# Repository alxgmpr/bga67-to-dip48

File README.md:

# bga67-to-dip48

Reusable bridge between the Google Home Mini's VFBGA67 NAND lands and a commercial XGecu
BGA-to-DIP48 socket adapter.

The architecture is intentionally asymmetric:

```text
PROGRAM                          BOOT / TEST

XGecu programmer                Google Home motherboard
       ^                                  ^
       | DIP48                            | solder balls
[ XGecu adapter ]                 [ chipless carrier A ]
[ actual NAND   ]                         |
       |                                 | DF40 service joint
       +------------------------> [ socket base B ]
                                  [ DIP48 receptacle ]
```

The actual NAND remains clamped in the XGecu adapter. That adapter/NAND assembly moves
between the programmer and board B. Board A is a permanent, chipless interposer soldered to
the Google motherboard; it has no NAND package and no sacrificial memory.

| Board | Contents | Nominal size |
|---|---|---:|
| `carrier/` | mirrored VFBGA67 motherboard lands + DF40 plug | 8.41 × 7.60 mm |
| `base/` | DIP48 socket for XGecu adapter + DF40 receptacle + passives | 27.78 × 61.38 mm |
| `chip/` | real VFBGA67 lands + DF40 receptacle, NAND soldered here | 8.41 × 7.60 mm |
| `prog/` | DF40 plug + DIP48 male pins for the XGecu T76 ZIF | 27.78 × 61.38 mm |

## Compact routed carrier

Board A follows the useful parts of Courk's original NandBug routing topology:

- the current compact 8.41 × 7.60 mm outline;
- top-side DF40 within 0.20 mm of the bottom-side mirrored VFBGA67 field centre;
- the completed carrier routing preserved as the canonical DF40 electrical order;
- one short diagonal dogbone from each used VFBGA67 land;
- ordinary 0.45 mm vias with 0.20 mm finished drills;
- no blind/buried vias, microvias, via-in-pad, fill/cap, or HDI process.

That last point holds for boards A, B and D. **Board C is the deliberate exception** — see
"Via-in-pad on board C" below.

The manufacturing target is a standard JLCPCB four-layer stackup, 1.6 mm, ENIG.

The 47 unused motherboard lands remain floating. `U1` is only a logical pin map and mirrored
land interface; it is excluded from BOM/position output and has no NAND model or package
graphics.

The carrier and the base are both routed. Base DRC reports zero unconnected items and zero
schematic parity issues; its remaining 20 warnings are all `text thickness out of range` on
silkscreen and are cosmetic.

## Via-in-pad on board C

Board C is the only board that puts vias inside BGA lands. The NAND is reflowed onto those
lands, which forces the choice:

- a soldermask-plugged via is not flat enough to print a stencil against when reballing;
- an untented via wicks solder out of the ball joint.

So board C's in-pad vias use JLCPCB's **Epoxy Filled & Capped** process: resin filled, baked,
levelled, then copper plated over to a flat surface. Via diameters must be 0.15–0.55 mm and
the vias must carry no soldermask opening on either face.

> **Pre-order gate.** JLCPCB document Epoxy Filled & Capped as the default at **6 layers and
> above** and do not list it as a standard 4-layer option. Board C is 4-layer. Confirm with
> JLCPCB that the process is available on a 4-layer order, and at what price, **before
> fabricating board C**. If it is not, the options are moving board C to 6 layers or routing
> the in-pad vias back out to dogbones.

Boards A, B and D remain free of via-in-pad and are unaffected. `tools/check_interposer.py`
still enforces the strict no-via-near-pad rule on carrier A, and enforces the fill-process
rules on board C: fillable drill range, minimum annular ring, via land no wider than the ball
land, and tenting on both faces.

## Mechanical load path

The DF40 pair normally remains mated. Routine removal happens at board B's DIP48 socket when
the complete XGecu adapter/NAND assembly moves to the programmer. The DIP48 socket and any
future standoffs/cradle must carry insertion force; it must not be reacted through the DF40,
carrier, or Google motherboard BGA lands.

## Verification

Close KiCad before scripted edits, then run:

```bash
make check
make panel
```

`tools/pinout.py` is the connector source of truth. `tools/check_interposer.py` guards the
chipless mirrored footprint, cross outline, same-number DF40 contract, ordinary through-via
dogbones, and absence of via-in-pad/HDI topology on carrier A. On board C, where via-in-pad is
intended, it instead enforces the Epoxy Filled & Capped rules: 0.15–0.55 mm fillable drills,
0.05 mm minimum annular ring, via land no wider than the ball land, and tenting on both faces.

`tools/bga_fit.py` checks BGA handedness: it fits a placed pad set against the normal land
pattern allowing rotation and translation only, and fails when the better fit is a reflection.

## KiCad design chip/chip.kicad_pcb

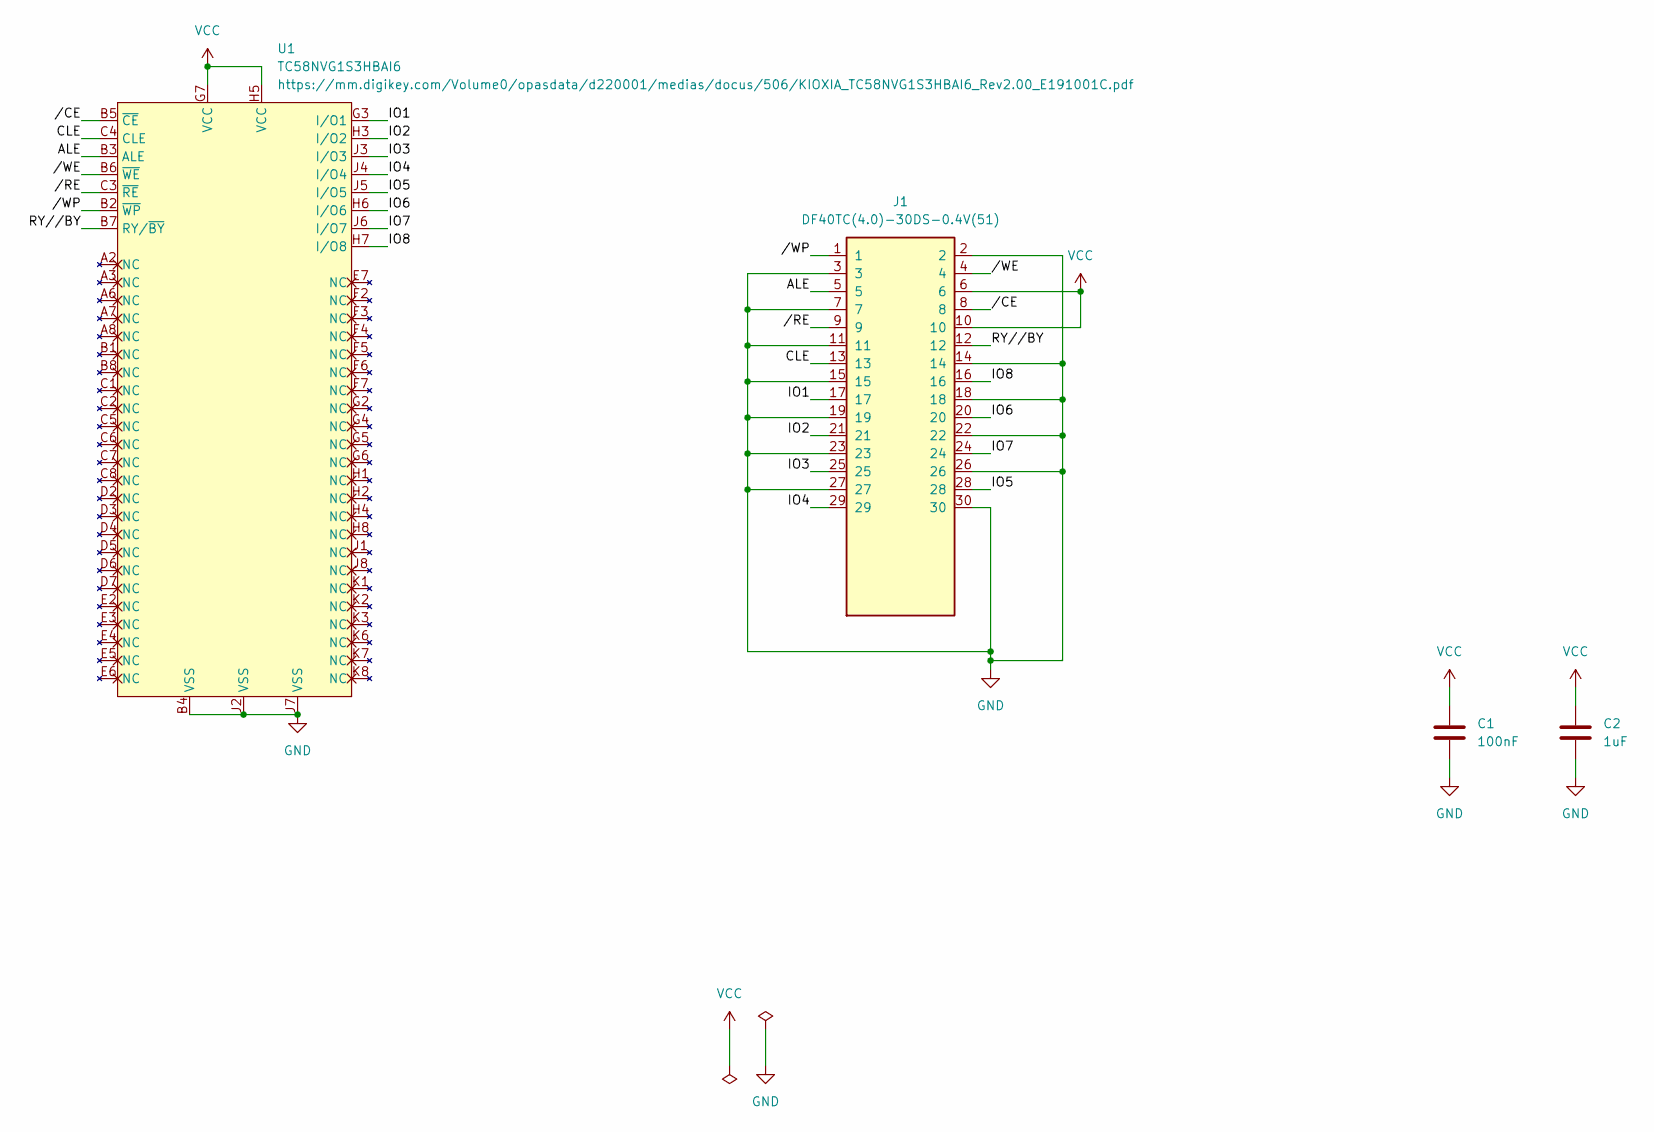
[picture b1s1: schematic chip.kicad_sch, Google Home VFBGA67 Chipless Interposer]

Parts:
C1: 100nF; C_0402_1005Metric
C2: 1uF; C_0402_1005Metric
J1: DF40TC(4.0)-30DS-0.4V(51); HIROSE_DF40TC_4.0_-30DS-0.4V_51_
U1: TC58NVG1S3HBAI6; BGA-67_6.5x8.0mm_Layout8x10_P0.8mm

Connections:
/ALE: J1.5, U1.B3 (ALE)
/CLE: J1.13, U1.C4 (CLE)
/IO1: J1.17, U1.G3 (I/O1)
/IO2: J1.21, U1.H3 (I/O2)
/IO3: J1.25, U1.J3 (I/O3)
/IO4: J1.29, U1.J4 (I/O4)
/IO5: J1.28, U1.J5 (I/O5)
/IO6: J1.20, U1.H6 (I/O6)
/IO7: J1.24, U1.J6 (I/O7)
/IO8: J1.16, U1.H7 (I/O8)
/RY//BY: J1.12, U1.B7 (RY/~BY)
//CE: J1.8, U1.B5 (~CE)
//RE: J1.9, U1.C3 (~RE)
//WE: J1.4, U1.B6 (~WE)
//WP: J1.1, U1.B2 (~WP)
GND: C1.2, C2.2, J1.2, J1.3, J1.7, J1.11, J1.14, J1.15, J1.18, J1.19, J1.22, J1.23, J1.26, J1.27, J1.30, U1.B4 (VSS), U1.J2 (VSS), U1.J7 (VSS)
VCC: C1.1, C2.1, J1.6, J1.10, U1.G7 (VCC), U1.H5 (VCC)

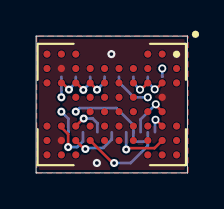
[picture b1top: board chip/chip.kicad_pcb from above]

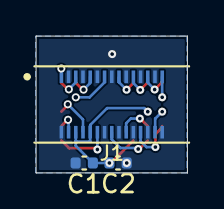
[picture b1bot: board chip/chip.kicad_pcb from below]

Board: 4 copper layers, 8.4 x 7.6 mm, 4 parts (3 on the bottom side), 17 nets.

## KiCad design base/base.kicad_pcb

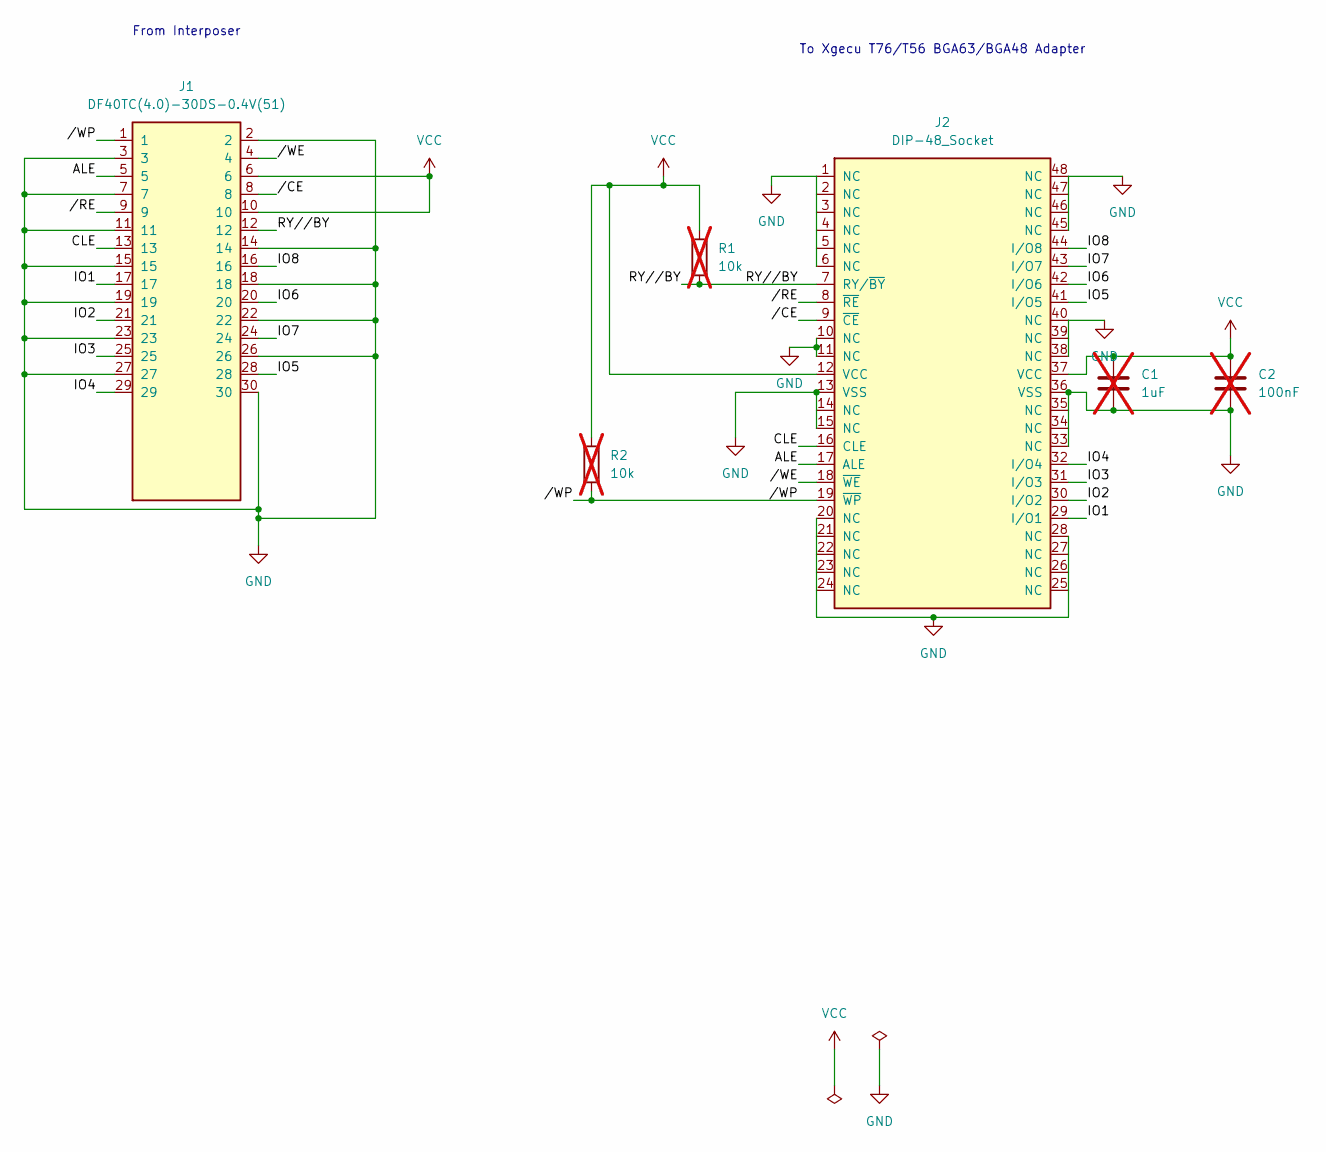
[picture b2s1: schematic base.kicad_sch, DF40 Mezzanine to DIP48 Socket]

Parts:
C1: 1uF; C_0603_1608Metric_Pad1.08x0.95mm_HandSolder; not fitted
C2: 100nF; C_0603_1608Metric_Pad1.08x0.95mm_HandSolder; not fitted
J1: DF40TC(4.0)-30DS-0.4V(51); HIROSE_DF40TC_4.0_-30DS-0.4V_51_
J2: DIP-48_Socket; DIP-48_SocketStrip_SMD_W15.24mm_P2.54mm
R1, R2: 10k; R_0603_1608Metric_Pad0.98x0.95mm_HandSolder; not fitted

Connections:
/ALE: J1.5, J2.17 (ALE)
/CLE: J1.13, J2.16 (CLE)
/IO1: J1.17, J2.29 (I/O1)
/IO2: J1.21, J2.30 (I/O2)
/IO3: J1.25, J2.31 (I/O3)
/IO4: J1.29, J2.32 (I/O4)
/IO5: J1.28, J2.41 (I/O5)
/IO6: J1.20, J2.42 (I/O6)
/IO7: J1.24, J2.43 (I/O7)
/IO8: J1.16, J2.44 (I/O8)
/RY//BY: J1.12, J2.7 (RY/~BY), R1.2
//CE: J1.8, J2.9 (~CE)
//RE: J1.9, J2.8 (~RE)
//WE: J1.4, J2.18 (~WE)
//WP: J1.1, J2.19 (~WP), R2.2
GND: C1.2, C2.2, J1.2, J1.3, J1.7, J1.11, J1.14, J1.15, J1.18, J1.19, J1.22, J1.23, J1.26, J1.27, J1.30, J2.1 (NC), J2.6 (NC), J2.10 (NC), J2.11 (NC), J2.13 (VSS), J2.15 (NC), J2.20 (NC), J2.28 (NC), J2.33 (NC), J2.36 (VSS), J2.38 (NC), J2.40 (NC), J2.45 (NC), J2.48 (NC)
VCC: C1.1, C2.1, J1.6, J1.10, J2.12 (VCC), J2.37 (VCC), R1.1, R2.1

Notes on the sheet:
To Xgecu T76/T56 BGA63/BGA48 Adapter
From Interposer

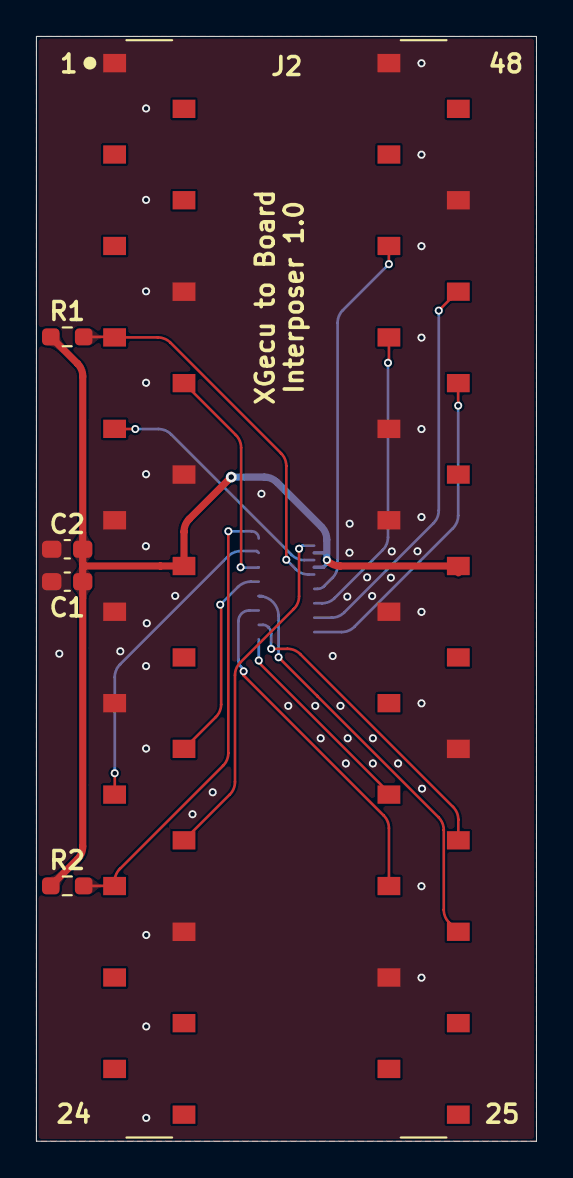
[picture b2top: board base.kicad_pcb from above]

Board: 4 copper layers, 27.8 x 61.4 mm, 6 parts (1 on the bottom side), 17 nets.

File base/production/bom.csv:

Designator,Footprint,Quantity,Value,LCSC Part #
J1,HIROSE_DF40TC_4.0_-30DS-0.4V_51_,1,DF40TC(4.0)-30DS-0.4V(51),
J2,DIP-48_SocketStrip_SMD_W15.24mm_P2.54mm,1,DIP-48_Socket,

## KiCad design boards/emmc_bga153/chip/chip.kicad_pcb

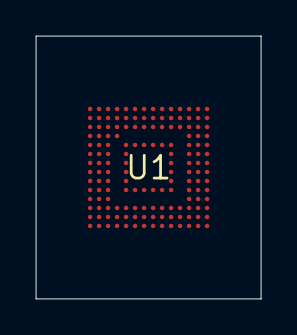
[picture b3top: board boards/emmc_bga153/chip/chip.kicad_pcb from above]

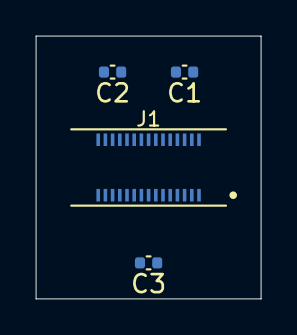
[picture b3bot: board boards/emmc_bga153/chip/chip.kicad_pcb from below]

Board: 4 copper layers, 12.5 x 14.6 mm, 5 parts (4 on the bottom side), 16 nets, no tracks yet.

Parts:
C1, C2: 1uF; C_0402_1005Metric
C3: 100nF; C_0402_1005Metric
J1: DF40TC(4.0)-30DS-0.4V(51); HIROSE_DF40TC_4.0_-30DS-0.4V_51_
U1: EMMC_BGA153_INTERFACE; BGA-153_emmc_bga153

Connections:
/CLK: J1.12, U1.M6
/CMD: J1.8, U1.M5
/DAT0: J1.17, U1.A3
/DAT1: J1.21, U1.A4
/DAT2: J1.25, U1.A5
/DAT3: J1.29, U1.B2
/DAT4: J1.28, U1.B3
/DAT5: J1.20, U1.B4
/DAT6: J1.24, U1.B5
/DAT7: J1.16, U1.B6
/DS: J1.9, U1.H5
/RST_n: J1.4, U1.K5
AUX_VDDI: C3.1, U1.C2
GND: C1.2, C2.2, C3.2, J1.2, J1.3, J1.7, J1.11, J1.14, J1.15, J1.18, J1.19, J1.22, J1.23, J1.26, J1.27, J1.30, U1.A6, U1.C4, U1.E7, U1.G5, U1.H10, U1.J5, U1.K8, U1.N2, U1.N5, U1.P4, U1.P6
VCC: C1.1, J1.6, U1.E6, U1.F5, U1.J10, U1.K9
VCCQ: C2.1, J1.10, U1.C6, U1.M4, U1.N4, U1.P3, U1.P5
